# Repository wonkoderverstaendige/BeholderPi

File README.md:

# Outline

- scalable array of networked camera nodes
- low-cost (relatively) ~100--200 Euro/node
- 800x600 @ 30 fps in visible or IR
- low latency preview of merged views
- synchronized to sub-millisecond time resolution
- hardware accelerated encoding
- synchronization with external systems (e.g. elecrophysiology recordings)

# Hardware

- [RaspberryPi 3B+/4B](https://www.raspberrypi.org/documentation/hardware/raspberrypi/README.md)
- [Raspberry/Picamera compatible camera module](https://www.raspberrypi.org/documentation/hardware/camera/README.md)
    - e.g. Camera Module v2 (8MP, FOV: 62.2° horizontal, 48.8° vertical)
    - **Read:** [How the PiCamera works](https://picamera.readthedocs.io/en/release-1.13/fov.html)
- [PoE hat](https://www.raspberrypi.org/products/poe-hat/) for power/network
- A decent receiving computer (ideally 1 CPU core/node)
- optional hardware encoding GPU
- PoE capable ethernet switch if PoE is used

# Software
- based on Picamera, ZMQ, OpenCV, FFmpeg

# Inspiration
## Raspicam paper
Inspiration of the system was taken from prior work done by [Saxena et al. 2018](https://www.physiology.org/doi/full/10.1152/jn.00215.2018),
[code here](https://github.com/DeshmukhLab/PicameraPaper).

# Installation
1) [System Overview](docs/SystemOverview.md)
2) [Beholder Installation](docs/Installation_Beholder.md)
3) [Eye Installation](docs/Installation_Eye.md)
4) [General Usage](docs/Usage.md)
5) [Troubleshooting](docs/Troubleshooting.md)

## Hardware
- [Camera Mounts](docs/CameraMounts.md)
- [Sync Lights](docs/SyncLights.md)

## Processing
- [Stitching](docs/processing/Stitching.md)
- [Synchronization](docs/Synchronization.md)
- [Tracing](docs/Tracing.md)
- [Tracking](docs/Tracking.md)

# TODO
- see [current todo list](docs/todo.md)

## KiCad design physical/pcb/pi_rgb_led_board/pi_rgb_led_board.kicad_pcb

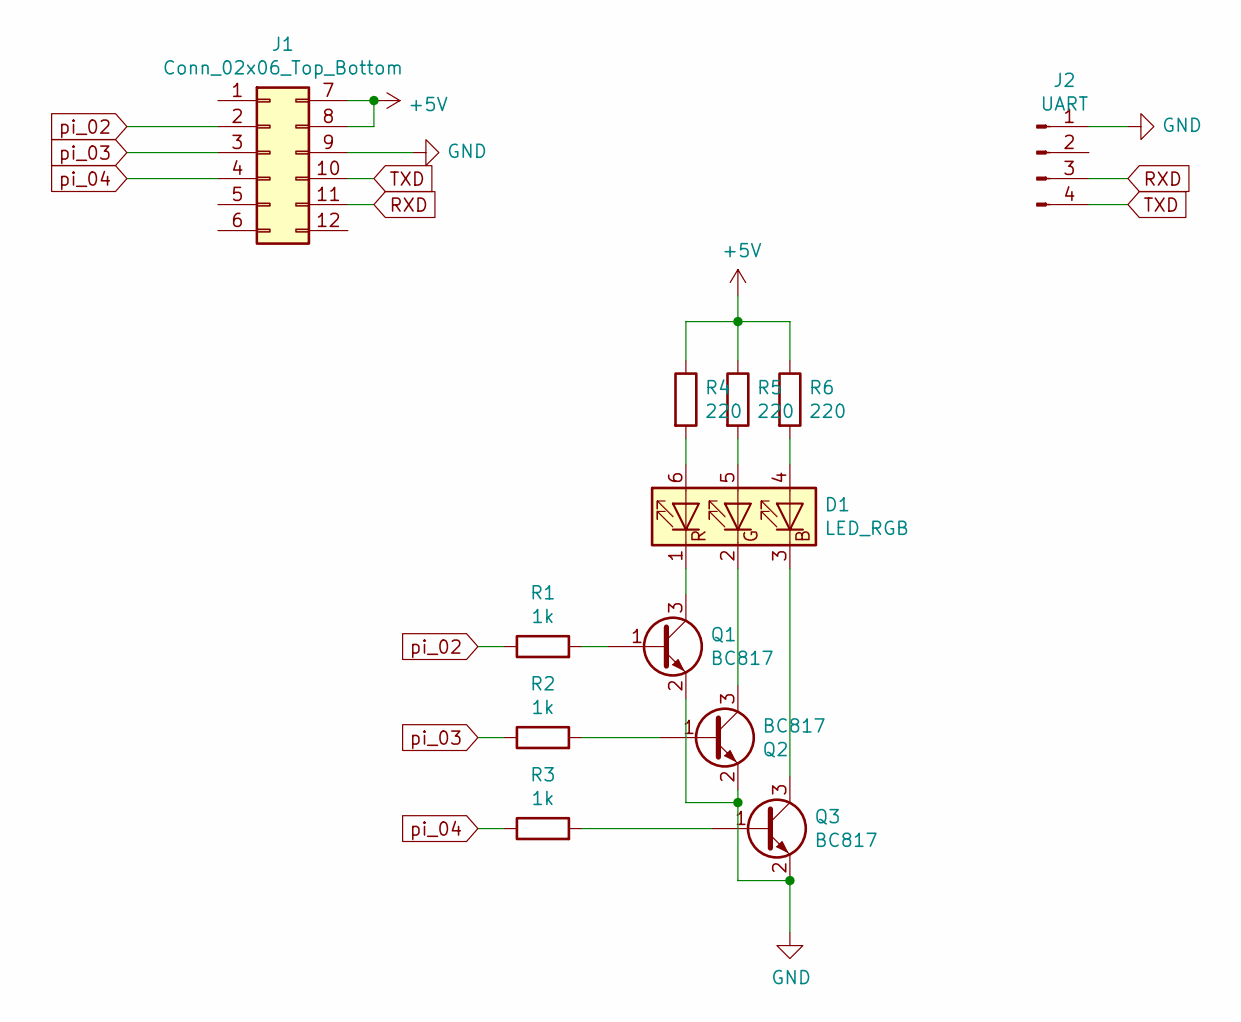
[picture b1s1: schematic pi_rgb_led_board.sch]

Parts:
D1: LED_RGB; LED_RGB_5050-6
J1: Conn_02x06_Top_Bottom; PinHeader_2x06_P1.27mm_Vertical
J2: UART; PinHeader_1x04_P1.27mm_Vertical
Q1, Q2, Q3: BC817; SOT-23
R1, R2, R3: 1k; R_0805_2012Metric
R4, R5, R6: 220; R_0805_2012Metric

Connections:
+5V: J1.7, J1.8, R4.1, R5.1, R6.1
GND: J1.9, J2.1, Q1.2 (E), Q2.2 (E), Q3.2 (E)
unnamed: D1.1 (RK), Q1.3 (C)
unnamed: D1.2 (GK), Q2.3 (C)
unnamed: D1.3 (BK), Q3.3 (C)
unnamed: D1.4 (BA), R6.2
unnamed: D1.5 (GA), R5.2
unnamed: D1.6 (RA), R4.2
unnamed: Q1.1 (B), R1.2
unnamed: Q2.1 (B), R2.2
unnamed: Q3.1 (B), R3.2
RXD: J1.11, J2.3
TXD: J1.10, J2.4
pi_02: J1.2, R1.1
pi_03: J1.3, R2.1
pi_04: J1.4, R3.1

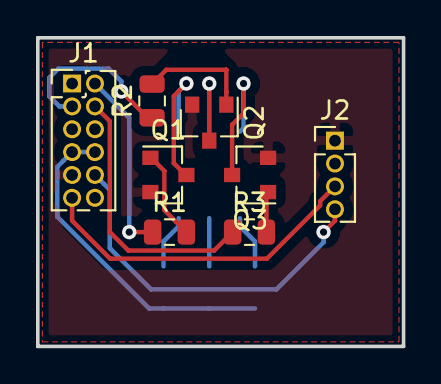
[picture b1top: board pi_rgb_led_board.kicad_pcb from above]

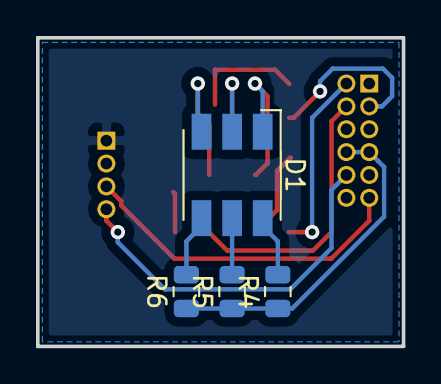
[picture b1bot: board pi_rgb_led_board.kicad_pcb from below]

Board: 2 copper layers, 20.3 x 17.1 mm, 12 parts (4 on the bottom side), 16 nets.

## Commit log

2019-01-25 Project specific .gitignore
2019-01-25 First working version
2019-01-25 README.md update
2019-01-25 Readme Update
2019-01-28 Update documentation
2019-01-28 Refactor piEye main
2019-01-28 Minor fixes
2019-01-28 Config file relocated
2019-01-28 Default telegraf configuration file
2019-01-28 Fix host telegraf configuration file
2019-01-28 debug option to drop n-th frames
2019-01-28 Debug message on intentional frame drops
2019-01-28 m: left over method call on int conversion
2019-01-28 Shuffle frame drops
2019-01-28 piEye logging hostname tag
2019-01-28 More information on frame skip event
2019-01-28 Rename Grabber and Writer threads, lower intentional frame drop rate
2019-01-28 Dropped frame message wording
2019-01-29 Bump framerate to 30 fps
2019-01-29 Fix filenaming scheme
2019-01-29 Fix frame source restart warning
2019-02-05 Bump framerate to 30.0 fps on Beholder
2019-02-05 Differentiate probable intentional frame drop and unexpected frame drop
2019-02-05 Start installation instructions
2019-02-05 Include raspbian image modification script
2019-02-05 Use Lite image, use SHA-256 on image download
2019-02-06 Systemd service announcing hostname and ip to gateway
2019-02-06 Switch announcing service to UDP broadcast
2019-02-06 Rename discovery service files
2019-02-07 Refine image generation script
2019-02-07 Overwrite base image on extraction to reset
2019-02-07 Barcode scanner
2019-02-07 Move discovery service into subdir
2019-02-07 Discovery receiver live host table
2019-02-07 Additional python dependencies on piEye install
2019-02-07 .gitignore Ansible retry files
2019-02-07 Check superuser privileges for image generation
2019-02-07 M: time formatting
2019-02-07 M: Formatting
2019-02-07 Fix issue with hostname resolution in discovery sender
2019-02-08 Ansible hostname setup and service reloading on update
2019-02-08 piEye streaming service installation
2019-02-08 Forgot the actual service file...
2019-02-08 More work on streaming service installation
2019-02-08 Allow ssh key location as parameter
2019-02-10 Network setup playbook
2019-02-10 Sort discovery list
2019-02-10 Update beholder IP source list to new configuration
2019-02-10 Add telegrafer role
2019-02-10 Main inventory file update for small host selection
2019-02-10 Expand Ansible roles and tasks
2019-02-10 Clean up barcode scan stub
2019-02-10 JSON payload for discovery packages
2019-02-10 Disable printing packet details
2019-02-10 Rework discovery receiver for more columns
2019-02-10 Copy public AND private keys to eyes to allow cross-ssh
2019-02-10 Disable stream duplication
2019-02-10 Fix telegraf agent output host specifier
2019-02-10 Move eye installer from roles to single playbook
2019-02-11 Show hostname in frame annotation
2019-02-11 Allow ssh pull from local network repo
2019-02-11 Add time difference column to discovery receiver
2019-02-11 Fix camera stream duplicatio config uptake by eye streamer
2019-02-11 Rename 'influxpi' to 'spectator'
2019-02-11 Add NTP setup and config
2019-02-12 Use chrony instead of timesyncd for NTP
2019-02-12 Beautify receiver a bit more
2019-02-12 Move network install tasks into eye_install.yml
2019-02-12 Fix status coloring
2019-02-12 Restart discovery sender with delay
2019-02-12 M: Cleanup
2019-02-12 Inventory in ansible.cfg
2019-02-12 Hardcode fps in ffmpeg command to 30 fps
2019-02-12 Test 24 stream performance
2019-02-12 Fix stream_duplication_parameter not taking effect
2019-02-12 Test 800x600 px performance
2019-02-12 Fix flipped frame shape for 800x600 test
2019-02-12 Match instance and file names to 1-indexed device IDs
2019-02-12 Increase heartbeat rate to 1Hz
2019-02-12 Reroll 1-indexed instance naming, just +1 file names
2019-02-12 Tighten discovery state tolerances
2019-02-12 Use hqdn3d denoiser in ffmpeg compressor
2019-02-12 Test 720p performance
2019-02-13 Again try to fix discovery service restart issues
2019-02-13 Drop to 800x600
2019-02-17 Resize fault/disconnect frames to match configuration
2019-02-17 Temp. disable annotations
2019-02-17 Force discovery restart harder
2019-02-17 Include spectator in update playbook
2019-02-17 Basic stitching demo
2019-02-17 Re-enable frame annotations
2019-02-17 Increase chrony update rate
2019-03-12 Remove unsused imports
2019-03-12 M: Rename script
2019-03-13 Initial setup.py
2019-05-06 Doc update
2019-05-06 Messing with ffmpeg options testing nvenc
2019-05-06 Bump grabber frame queue size from half a second to around 5 seconds
2019-05-06 Reduce display refresh rate
2019-05-06 Ignore dead threads on shutdown
2019-05-06 Simplify display frame buffer. GIL takes care of shared array access.
2019-05-08 Update MAC:hostname mapping
2019-05-08 Conditionally flip frames
2019-05-08 Temporary username change on beholder git source
2019-05-08 Ignore apt warnings when no internet available
2019-05-08 Crude distance measure for calibration
2019-05-08 Fancier crude distance measure for calibration
2019-05-08 Even fancier crude distance measure for calibration
2019-05-09 Add center calibration cross-hair
2019-05-09 Stop center calibration cross-hair from blinking
2019-05-11 Rename zmq topic
2019-05-11 Add chrony config for Beholder
2019-05-11 Add spectator to chrony sources (not in use though)
2019-05-11 rename chrony configuration templates
2019-05-11 Host specific frame flip option
2019-05-11 eye zmq topic handling update
2019-05-11 eye flip list fix
2019-05-11 Disable intentional frame drop as productive use nears
2019-05-11 Rename and clean up eye installation playbook
2019-05-11 Frame flip for bottom row to move metadata out of ROI
2019-05-12 Rename discovery service sender file for eyes
2019-05-12 Basic playbook to install Beholder computer
2019-05-12 Measurement tool improvement
2019-05-12 Factor out frame annotation
2019-05-13 Hardware encoding!!!
2019-05-13 Remove an annoying print
2019-05-13 Disable unused python dependencies
2019-05-13 Don't fail disabling openntp when not installled
2019-05-14 Display cropped preview with cropping parameters.
2019-05-14 Refine calibration tool
2019-05-14 Some TODO notes
2019-05-27 Write per-session log file
2019-05-27 Adjust x-cropping for actual setting
2019-05-27 Trial duration on/off trigger
2019-05-27 Disable debug crosshairs
2019-05-27 Trial/recording state indicator
2019-05-28 TODO update
2019-05-28 Write data sets into single directory.
2019-05-28 Change default output directory
2019-05-28 Remove unused command line crop options
2019-05-28 Testing new eye debug print
2019-05-28 callback frame number in image
2019-05-28 Wiggle recording indicator around a bit
2019-06-01 Move euclidean_distance helper function to utilities
2019-06-01 Initial Tracer tool for manual tracking
2019-06-01 Initial Graph primitives for MazeGraph
2019-06-01 Allow single row display
2019-06-01 Optional device-local beholder config and config file CLI parameter
2019-06-01 Address YAML Loader Deprecation warning
2019-06-01 Relocate tools directory to more prominent location
2019-06-02 Update tracer with more accurate node distance calculations
2019-06-02 Reformat click response and node annotation
2019-06-02 MazeGraph prototype expansion
2019-06-02 Add missing bridge
2019-06-02 Shift main to separate function for future call from CLI entry point
2019-06-02 More requirements in setup.py
2019-06-03 Allow relocating a selected node
2019-06-03 Add recording button debounce time to prevent trigger spam
2019-06-03 Move rec button debounce logic around to account for trial-trigger start
2019-06-14 Fix unresolved local cfg variable
2019-06-14 M: Spelling
2019-06-14 Add shebang to exectue piEye main in python 3 by default
2019-06-14 Argument parsing and check to use local over default config on piEyes
2019-06-14 python3.5 on eyes doesn't have format strings yet...
2019-06-14 More python3.5 fixes on pieyes
2019-07-16 Adjust button code to trigger trial by Logitech presenter
2019-07-16 Minor fixes to tracer tool
2019-07-17 Minimalistic tracker demo
2019-07-17 Crop'n'stitch script
2019-07-17 Hwardware accelerated stitching
2019-07-17 Default node list (Juraj's)
2019-07-23 Start multipart message transmission
2019-07-23 command message exchange prototype
2019-07-23 command message exchange prototype pt. 2
2019-07-23 Bump mjpeg stream bitrate from 17 Mbps to 25 Mbps
2019-07-23 Print camera metadata for testing
2019-07-23 metadata packing
2019-07-23 more metadata packing
2019-07-23 metadata packaging issues
2019-07-23 more packaging issues
2019-07-23 Metadata propagation and logging
2019-07-23 Pausable flag or pausing during debugging
2019-07-23 Manual AWB mode
2019-07-23 Fix yml gains readout
2019-07-25 Store frame sizes
2019-07-25 Manual white balance option
2019-07-25 Tracer log file format dataset name prefix
2019-07-25 Cropping override CLI flag
2019-07-25 Allow deprecated single- and current multipart transfers from zmq
2019-07-25 Fix issue looking for local pieye config
2019-07-25 Disable unused command input socket
2019-07-25 Fixed brightness and white balance defaults
2019-07-25 fix typo in config. Argh.
2019-07-25 Temporary auto whitebalance re-enable
2019-07-26 Set brightness to default 50 for last experiment
2019-07-26 Experimental exposure settings v01
2019-07-26 Experimental exposure settings v02
2019-07-27 Reduce tracer UI wait time
2019-07-29 empty blink sketch
2019-10-10 Improve ffmpeg pupe failure handling and reporting
2019-10-11 Create output and logging directories if needed
2019-10-11 VERY obvious recording fault indicator
2019-10-11 Quietened log output in non-debug mode
2019-10-11 Warn when disk space low, stop when too little space available.
2019-10-11 Fix logging debug flag not doing anything
2019-10-14 Initial repair script to stitch with missing camera views
2019-10-17 Fix off-by-one error in the ids of missing eyes
2019-11-12 Limit hostname length to match expected metadata dtype
2020-02-01 Hardware decoding of mjpeg streams
2020-02-01 Dummy Server prototype
2020-02-01 Move old stitcher into tools collection
2020-02-01 New stitcher using perspective correction
2020-02-01 Fix non-square frame creation
2020-02-02 Allow flipped camera views for stitch-align
2020-02-02 Allow skipping frames to compensate frame rate differences
2020-02-04 targets
2020-02-04 RGB board prototype
2020-02-04 Documentation update
2020-02-13 Include frame naming offset parameter
2020-06-24 ffmpeg with nvenc initial documentation
2020-06-27 eye image prep checksum chnages
2020-06-27 Incremental image prep script updates
2021-03-08 Update raspbian image download
2022-04-13 eye image generation updated to raspberrypi OS with custom user
2022-04-14 streaming service to temporary new user
2022-04-14 Enable MAC in discovery packets
2022-04-14 Disable telemetry and use new user name in ansible eye setup
2022-04-14 Revert all Bullseye changes of username and use Buster
2022-04-28 Initial PXE/Network boot setup
2022-06-06 Initial PXE/Network boot setup part 2
2022-06-08 Add simple alignment markers
2022-06-08 .gitignore vscode
2022-06-09 PXE boot refinement
2022-06-09 Fix zero-indexed camera labels in videos
2023-03-23 Truncation resistant recording startup
2023-03-23 Default launcher scripts
2023-03-23 Streamlined install requirements
2023-03-23 fix launcher paths
2023-03-23 Initial readme changes
2023-03-23 readme bump
2023-03-23 readme fix logo
2023-03-23 really readme fix logo
2023-03-23 add .gitattributes for linguist
